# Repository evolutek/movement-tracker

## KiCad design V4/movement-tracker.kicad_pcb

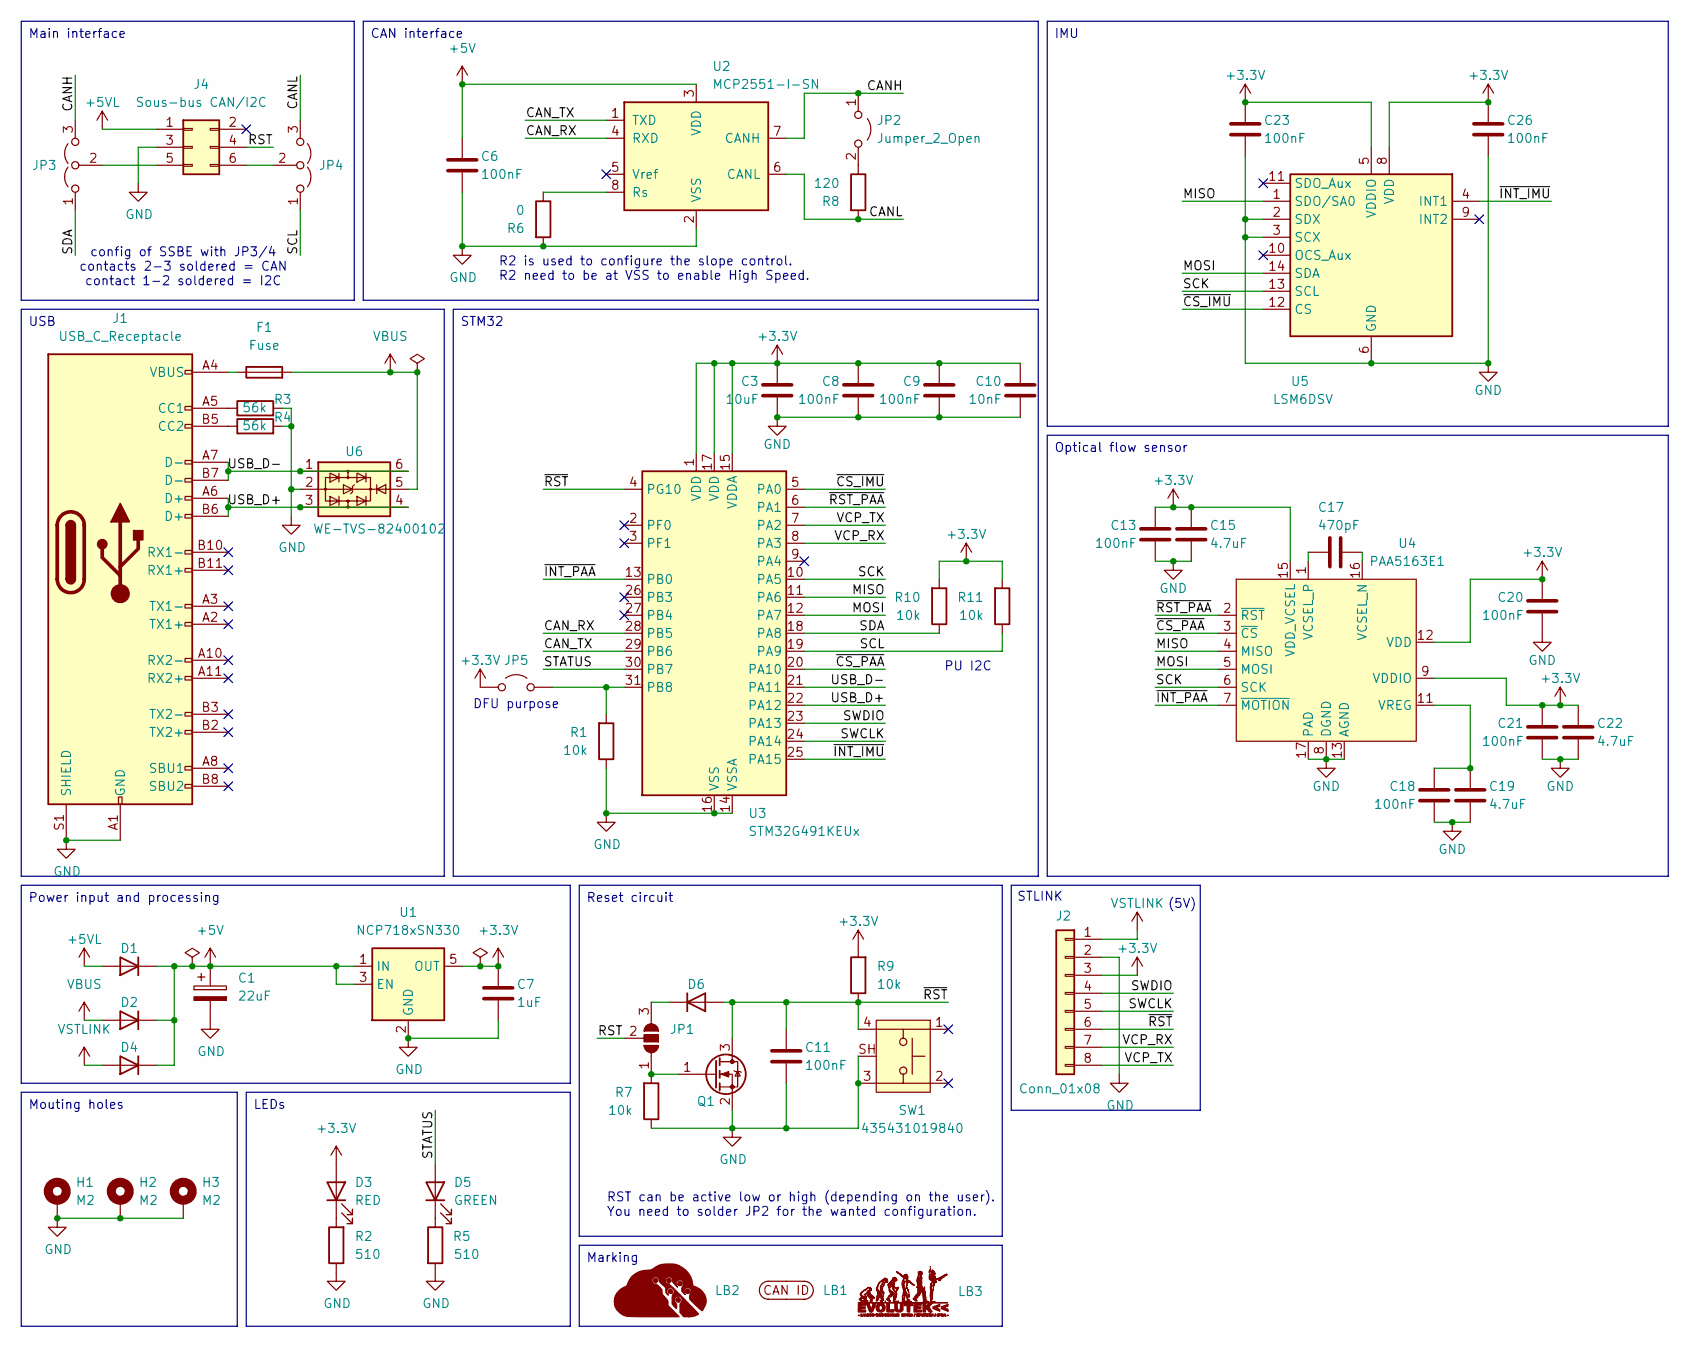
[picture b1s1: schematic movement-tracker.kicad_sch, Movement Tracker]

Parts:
C1: 22uF; CP_Elec_3x5.4
C3: 10uF; C_0603_1608Metric
C6, C8, C9, C11, C13, C18, C20, C21, C23, C26: 100nF; C_0603_1608Metric
C7: 1uF; C_0603_1608Metric
C10: 10nF; C_0603_1608Metric
C15, C19, C22: 4.7uF; C_0603_1608Metric
C17: 470pF; C_0603_1608Metric
D1, D2, D4, D6: D; D_SOD-523
D3: RED; LED_0805_2012Metric
D5: GREEN; LED_0805_2012Metric
F1: Fuse; Fuse_0805_2012Metric
H1, H2, H3: M2; MountingHole_2.2mm_M2_Pad_Via
J1: USB_C_Receptacle; 632722110112
J2: Conn_01x08; 686108188822
J4: Sous-bus CAN/I2C; 690367280676
JP1: SolderJumper_3_Bridged12; SolderJumper-3_P1.3mm_Open_RoundedPad1.0x1.5mm_NumberLabels
JP2, JP5: Jumper_2_Open; SolderJumper-2_P1.3mm_Open_RoundedPad1.0x1.5mm
JP3, JP4: Jumper_3_Open; SolderJumper-3_P1.3mm_Open_RoundedPad1.0x1.5mm_NumberLabels
LB1: CAN ID Label
LB2: LOGO; Logo Aisler Min
LB3: LOGO; logo-evo-min
Q1: Q_NMOS_GSD; SOT-23
R1, R7, R9, R10, R11: 10k; R_0603_1608Metric
R2, R5: 510; R_0603_1608Metric
R3, R4: 56k; R_0603_1608Metric
R6: 0; R_0603_1608Metric
R8: 120; R_0603_1608Metric
SW1: 435431019840
U1: NCP718xSN330; SOT-23-5
U2: MCP2551-I-SN; SOIC-8_3.9x4.9mm_P1.27mm
U3: STM32G491KEUx; QFN-32-1EP_5x5mm_P0.5mm_EP3.45x3.45mm-Without thermal pad
U4: PAA5163E1
U5: LSM6DSV; LGA-14_3x2.5mm_P0.5mm_LayoutBorder3x4y
U6: WE-TVS-82400102; SOT-23-6

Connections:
+3.3V: C3.1, C7.1, C8.1, C9.1, C10.1, C13.2, C15.2, C20.2, C21.2, C22.2, C23.1, C26.1, D3.2 (A), J2.3, JP5.1 (A), R9.2, R10.2, R11.2, U1.5 (OUT), U3.1 (VDD), U3.15 (VDDA), U3.17 (VDD), U4.9 (VDDIO), U4.12 (VDD), U4.15 (VDD_VCSEL), U5.5 (VDDIO), U5.8 (VDD)
+5V: C1.1, C6.1, D1.1 (K), D2.1 (K), D4.1 (K), U1.1 (IN), U1.3 (EN), U2.3 (VDD)
+5VL: D1.2 (A), J4.1
/CANH: JP2.1 (A), JP3.3 (B), U2.7 (CANH)
/CANL: JP4.3 (B), R8.2, U2.6 (CANL)
/CAN_RX: U2.4 (RXD), U3.28 (PB5)
/CAN_TX: U2.1 (TXD), U3.29 (PB6)
/MISO: U3.11 (PA6), U4.4 (MISO), U5.1 (SDO/SA0)
/MOSI: U3.12 (PA7), U4.5 (MOSI), U5.14 (SDA)
/RST: J4.4, JP1.2 (C)
/SCK: U3.10 (PA5), U4.6 (SCK), U5.13 (SCL)
/SCL: JP4.1 (A), R11.1, U3.19 (PA9)
/SDA: JP3.1 (A), R10.1, U3.18 (PA8)
/STATUS: D5.2 (A), U3.30 (PB7)
/SWCLK: J2.5, U3.24 (PA14)
/SWDIO: J2.4, U3.23 (PA13)
/USB_D+: J1.A6 (D+), J1.B6 (D+), U3.22 (PA12), U6.3, U6.4
/USB_D-: J1.A7 (D-), J1.B7 (D-), U3.21 (PA11), U6.1, U6.6
/VCP_RX: J2.7, U3.8 (PA3)
/VCP_TX: J2.8, U3.7 (PA2)
/~CS_IMU: U3.5 (PA0), U5.12 (CS)
/~CS_PAA: U3.20 (PA10), U4.3 (~CS)
/~INT_IMU: U3.25 (PA15), U5.4 (INT1)
/~INT_PAA: U3.13 (PB0), U4.7 (~MOTION)
/~RST_PAA: U3.6 (PA1), U4.2 (~RST)
/~RST: C11.1, D6.2 (A), J2.6, Q1.3 (D), R9.1, SW1.4, U3.4 (PG10)
GND: C1.2, C3.2, C6.2, C7.2, C8.2, C9.2, C10.2, C11.2, C13.1, C15.1, C18.1, C19.1, C20.1, C21.1, C22.1, C23.2, C26.2, H1.1, H2.1, H3.1, J1.A1 (GND), J1.A12 (GND), J1.B1 (GND), J1.B12 (GND), J1.S1 (SHIELD), J2.2, J4.3, Q1.2 (S), R1.1, R2.1, R3.2, R4.2, R5.2, R6.2, R7.1, SW1.3, SW1.SH, U1.2 (GND), U2.2 (VSS), U3.14 (VSSA), U3.16 (VSS), U3.32 (VSS), U4.8 (DGND), U4.13 (AGND), U4.17 (PAD), U5.2 (SDX), U5.3 (SCX), U5.6 (GND), U5.7 (GND), U6.2
unnamed: D3.1 (K), R2.2
unnamed: D5.1 (K), R5.1
unnamed: D6.1 (K), JP1.3 (B)
unnamed: F1.1, J1.A4 (VBUS), J1.A9 (VBUS), J1.B4 (VBUS), J1.B9 (VBUS)
unnamed: J1.A5 (CC1), R3.1
unnamed: J1.B5 (CC2), R4.1
unnamed: J4.5, JP3.2 (C)
unnamed: J4.6, JP4.2 (C)
unnamed: JP1.1 (A), Q1.1 (G), R7.2
unnamed: JP2.2 (B), R8.1
unnamed: JP5.2 (B), R1.2, U3.31 (PB8)
unnamed: R6.1, U2.8 (Rs)
unnamed: C17.1, U4.16 (VCSEL_N)
unnamed: C17.2, U4.1 (VCSEL_P)
unnamed: C18.2, C19.2, U4.11 (VREG)
VBUS: D2.2 (A), F1.2, U6.5
VSTLINK: D4.2 (A), J2.1

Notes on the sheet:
(5V)
PU I2C
DFU purpose
config of SSBE with JP3/4 contacts 2-3 soldered = CAN contact 1-2 soldered = I2C
STLINK
RST can be active low or high (depending on the user). You need to solder JP2 for the wanted configuration.
R2 is used to configure the slope control. R2 need to be at VSS to enable High Speed.
Optical flow sensor
Power input and processing
Reset circuit
IMU
CAN interface
Mouting holes
USB
Marking
STM32
LEDs
Main interface

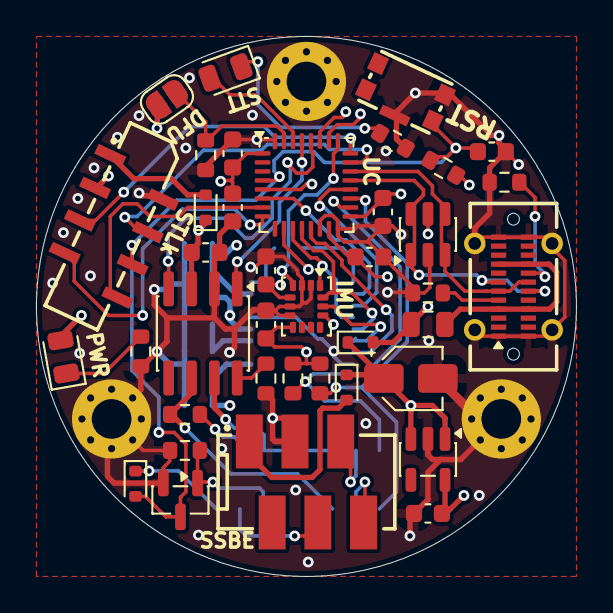
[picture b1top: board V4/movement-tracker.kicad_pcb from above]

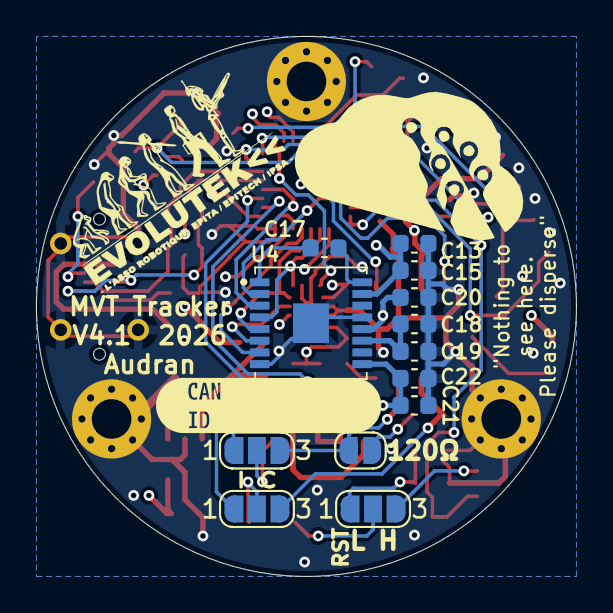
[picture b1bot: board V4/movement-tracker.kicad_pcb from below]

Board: 4 copper layers, 30.0 x 30.0 mm, 58 parts (16 on the bottom side), 44 nets.

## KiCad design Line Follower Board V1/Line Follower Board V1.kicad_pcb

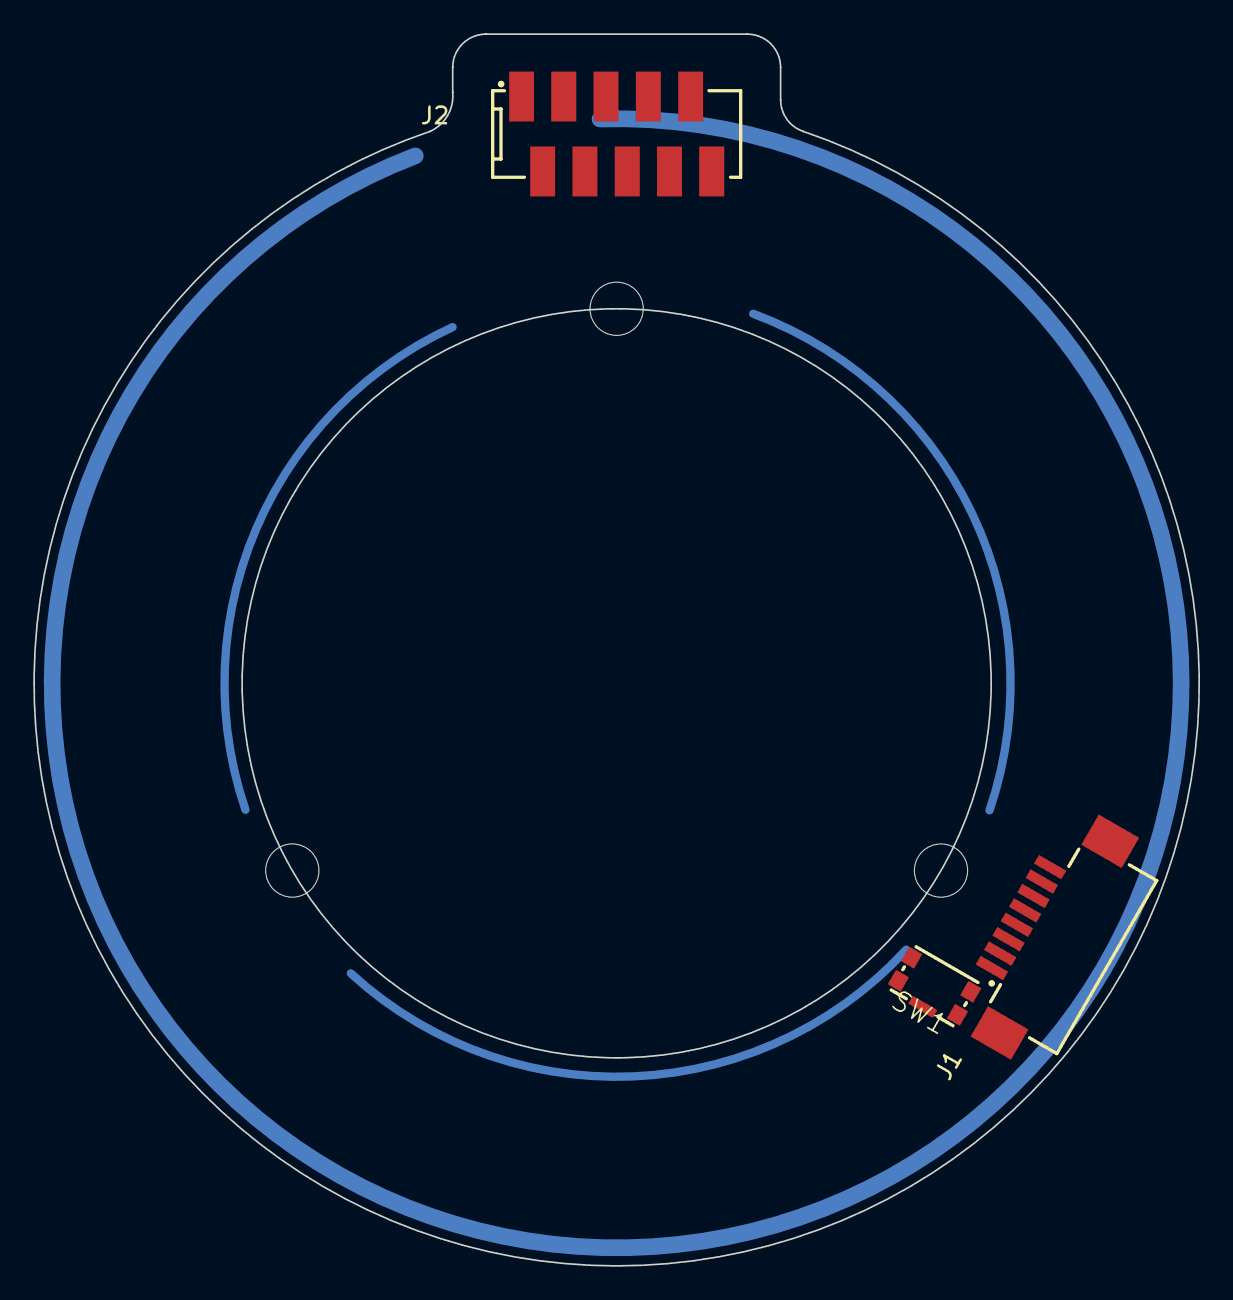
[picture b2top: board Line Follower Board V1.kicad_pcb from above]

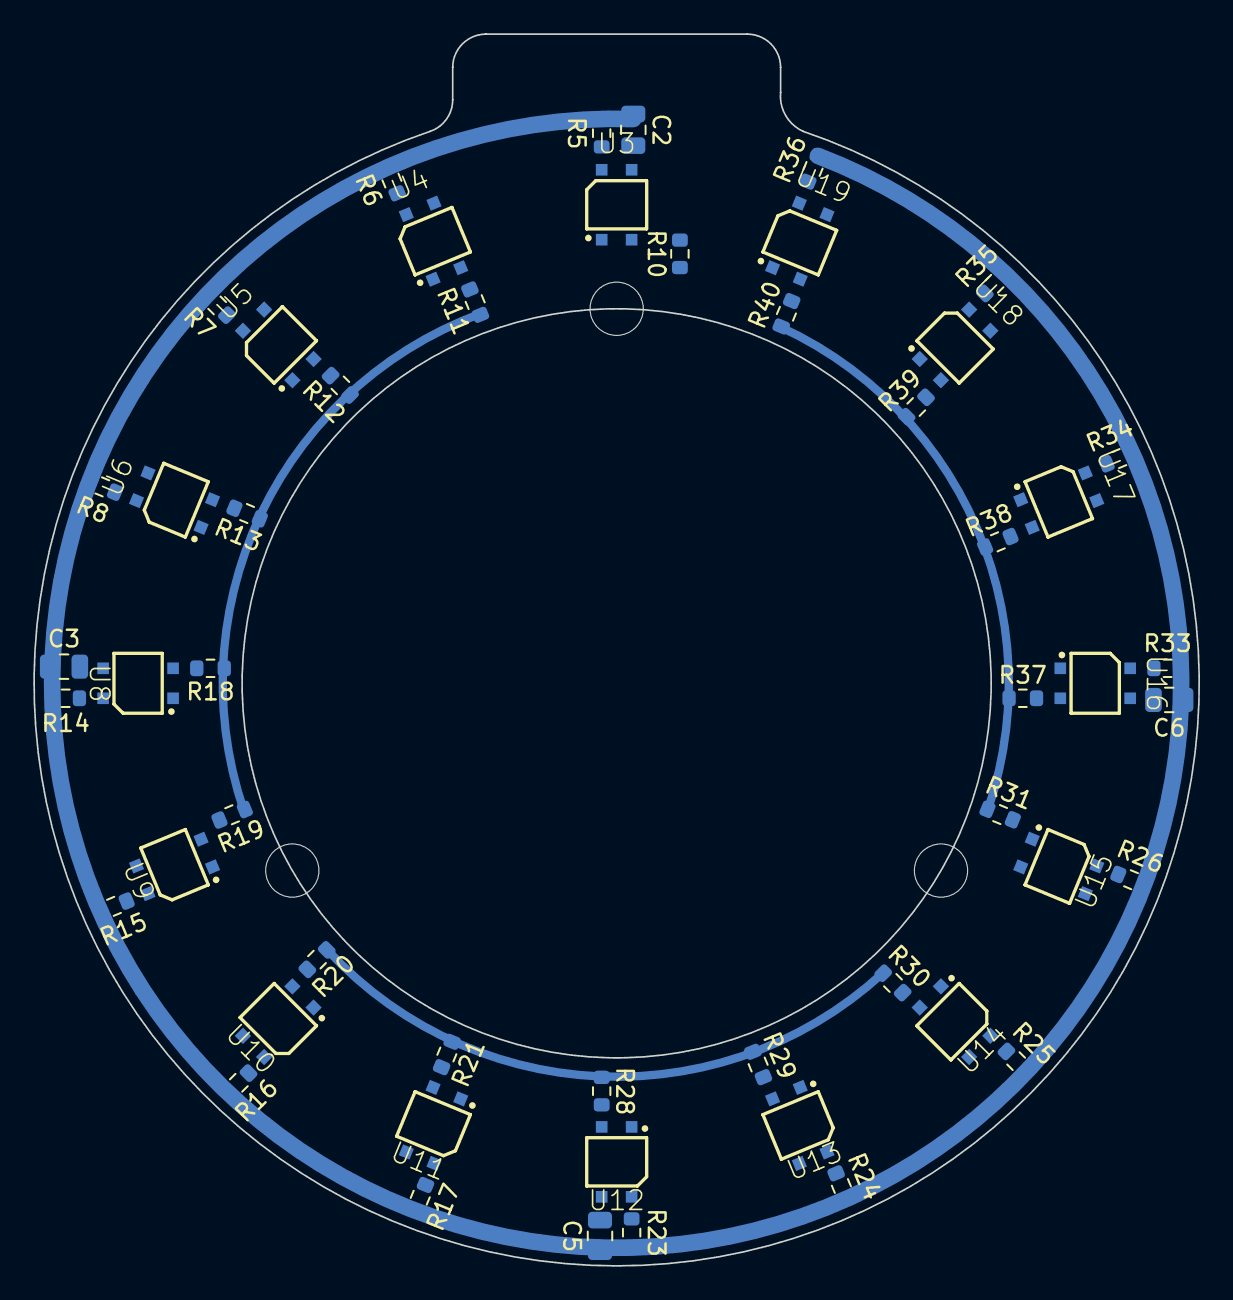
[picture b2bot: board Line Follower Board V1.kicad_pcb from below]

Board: 2 copper layers, 70.0 x 74.0 mm, 58 parts (52 on the bottom side), 36 nets, no tracks yet.

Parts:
C2, C3, C5, C6: 22uF; C_0805_2012Metric
H1, H2, H3: M3; MountingHole_3.2mm_M3
J1: STLINK-EVO; 686108188622
J2: Bus Actuators; 690367281076
R5, R6, R7, R8, R14, R15, R16, R17, R23, R24, R25, R26, R33, R34, R35, R36: 100; R_0603_1608Metric
R10, R11, R12, R13, R18, R19, R20, R21, R28, R29, R30, R31, R37, R38, R39, R40: 10k; R_0603_1608Metric
SW1: 435431019840
U3, U4, U5, U6, U8, U9, U10, U11, U12, U13, U14, U15, U16, U17, U18, U19: 1642730961200; WL-OSEN_2734_1642730961200

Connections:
+3.3V: J1.1, R10.1, R11.1, R12.1, R13.1, R18.1, R19.1, R20.1, R21.1, R28.1, R29.1, R30.1, R31.1, R37.1, R38.1, R39.1, R40.1
+5V: C2.1, C3.1, C5.1, C6.1, J2.1, R5.1, R6.1, R7.1, R8.1, R14.1, R15.1, R16.1, R17.1, R23.1, R24.1, R25.1, R26.1, R33.1, R34.1, R35.1, R36.1
/SENSOR1: R10.2, U3.4
/SENSOR2: R11.2, U4.4
/SENSOR3: R12.2, U5.4
/SENSOR4: R13.2, R18.2, U6.4, U8.4
/SENSOR5: R19.2, U9.4
/SENSOR6: R20.2, U10.4
/SENSOR7: R21.2, U11.4
/SENSOR8: R28.2, U12.4
/SENSOR10: R29.2, U13.4
/SENSOR11: R30.2, U14.4
/SENSOR12: R31.2, U15.4
/SENSOR13: R37.2, U16.4
/SENSOR14: R38.2, U17.4
/SENSOR15: R39.2, U18.4
/SENSOR16: R40.2, U19.4
/~RST: J1.5, SW1.4
GND: J1.4, J1.8, J1.MP (MountPin), J2.3, J2.4, SW1.3, SW1.SH, U3.3, U4.3, U5.3, U6.3, U8.3, U9.3, U10.3, U11.3, U12.3, U13.3, U14.3, U15.3, U16.3, U17.3, U18.3, U19.3
GNDS: C2.2, C3.2, C5.2, C6.2, U3.1 (K), U4.1 (K), U5.1 (K), U6.1 (K), U8.1 (K), U9.1 (K), U10.1 (K), U11.1 (K), U12.1 (K), U13.1 (K), U14.1 (K), U15.1 (K), U16.1 (K), U17.1 (K), U18.1 (K), U19.1 (K)
unnamed: R5.2, U3.2 (A)
unnamed: R6.2, U4.2 (A)
unnamed: R7.2, U5.2 (A)
unnamed: R8.2, U6.2 (A)
unnamed: R14.2, U8.2 (A)
unnamed: R15.2, U9.2 (A)
unnamed: R16.2, U10.2 (A)
unnamed: R17.2, U11.2 (A)
unnamed: R23.2, U12.2 (A)
unnamed: R24.2, U13.2 (A)
unnamed: R25.2, U14.2 (A)
unnamed: R26.2, U15.2 (A)
unnamed: R33.2, U16.2 (A)
unnamed: R34.2, U17.2 (A)
unnamed: R35.2, U18.2 (A)
unnamed: R36.2, U19.2 (A)

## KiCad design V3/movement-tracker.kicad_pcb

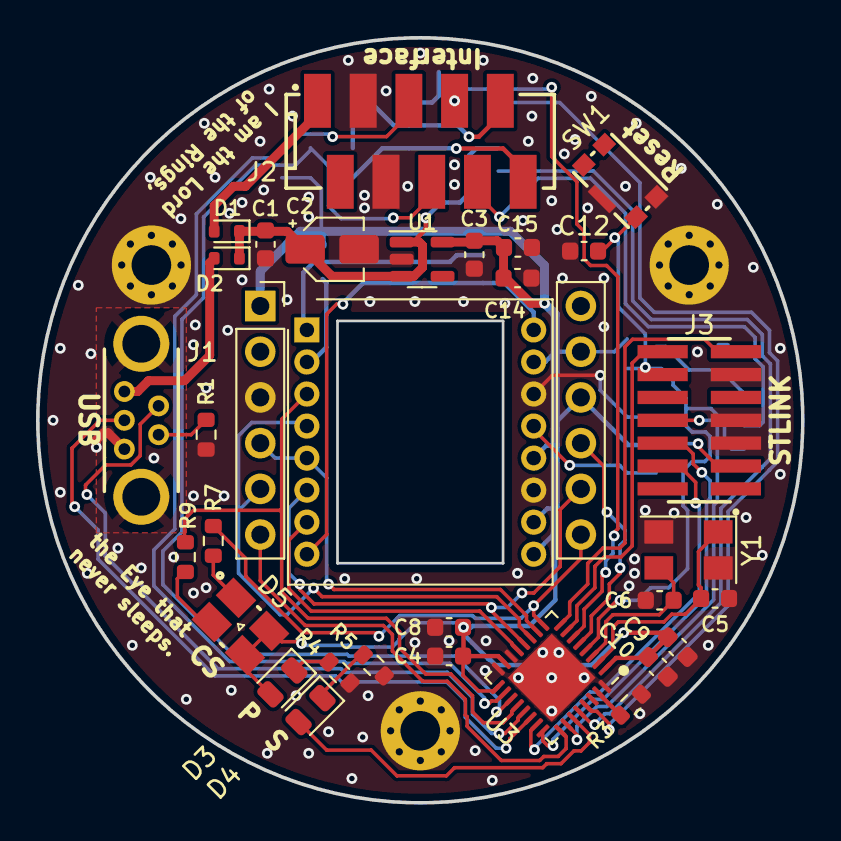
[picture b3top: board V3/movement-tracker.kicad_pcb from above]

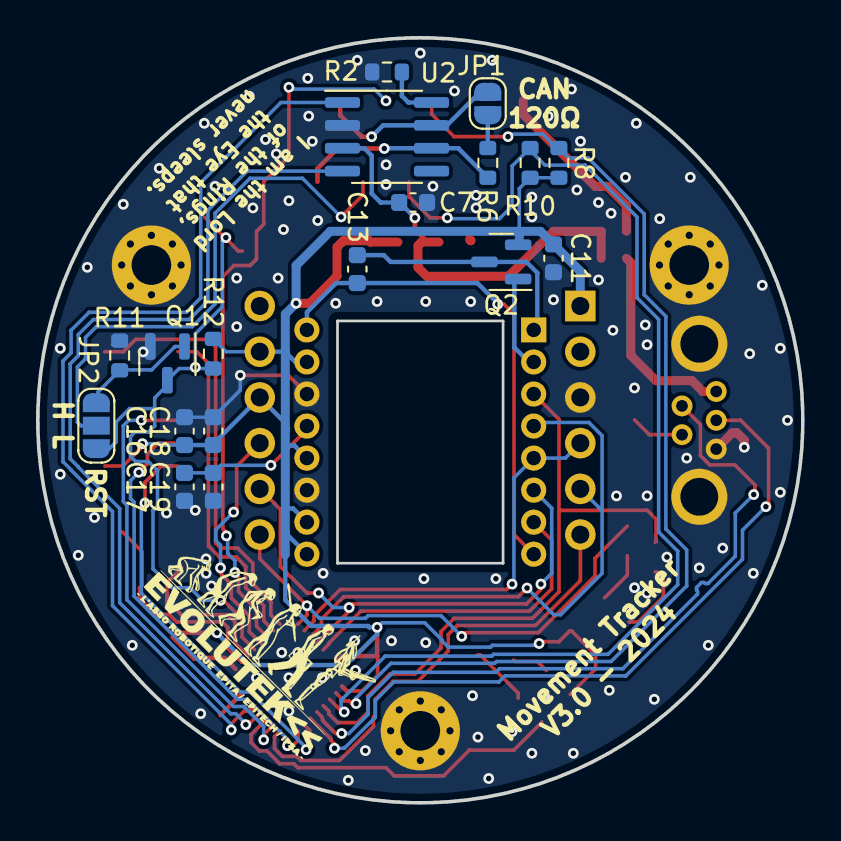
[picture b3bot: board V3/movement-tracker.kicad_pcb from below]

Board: 2 copper layers, 42.5 x 42.5 mm, 53 parts (18 on the bottom side), 45 nets.

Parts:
C1, C3, C15: 1uF; C_0603_1608Metric
C2: 100uF; CP_Elec_3x5.4
C4, C19: 10uF; C_0603_1608Metric
C5, C6: 18pF; C_0603_1608Metric
C7, C8, C9, C11, C12, C14, C16, C17: 100nF; C_0603_1608Metric
C10: 10nF; C_0603_1608Metric
C13: 470p; C_0603_1608Metric
C18: 3.3uF; C_0603_1608Metric
D1, D2: D; D_SOD-523
D3: RED; LED_0805_2012Metric
D4: GREEN; LED_0805_2012Metric
D5: 150121YV74000; WL-SBCW_1210
H1, H2, H3: M2; MountingHole_2.2mm_M2_Pad_Via
J1: USB_B_Mini; 651005136421
J2: Bus Actuators; 690367281076
J3: STLINK; SAMTEC_FTSH-107-01-L-DV-K
JP1: Jumper_2_Open; SolderJumper-2_P1.3mm_Open_RoundedPad1.0x1.5mm
JP2: SolderJumper_3_Bridged12; SolderJumper-3_P1.3mm_Open_RoundedPad1.0x1.5mm_NumberLabels
Q1: Q_NMOS_GSD; SOT-23
Q2: Q_PMOS_GSD; SOT-23
R1: 100k; R_0603_1608Metric
R2: 0; R_0603_1608Metric
R3, R11, R12: 10k; R_0603_1608Metric
R4, R5, R7, R9: 510; R_0603_1608Metric
R6: 120; R_0603_1608Metric
R8, R10: 4.7k; R_0603_1608Metric
SW1: 435431019840
U1: NCP718xSN330; SOT-23-5
U2: MCP2551-I-SN; SOIC-8_3.9x4.9mm_P1.27mm
U3: STM32G491KEUx; QFN-32-1EP_5x5mm_P0.5mm_EP3.45x3.45mm
U4: BNO085; Adafruit BNO085
U5: ADNS 9800
Y1: 16 MHz; Crystal_SMD_5032-4Pin_5.0x3.2mm

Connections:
+3.3V: C3.1, C4.1, C8.1, C9.1, C10.1, C11.1, C14.1, C15.1, C16.1, C18.1, D3.2 (A), D5.3 (AG), D5.4 (AY), J3.3, Q2.2 (S), R8.1, R10.1, R12.2, U1.5 (OUT), U3.1 (VDD), U3.15 (VDDA), U3.17 (VDD), U4.1 (VIN), U4.8 (P0), U4.9 (P1), U5.9 (VDD), U5.10 (PWR_OPT), U5.12 (VDD3), U5.15 (VDDIO)
+5V: C1.1, C2.1, C7.1, D1.1 (K), D2.1 (K), U1.1 (IN), U1.3 (EN), U2.3 (VDD)
+5VA: D1.2 (A), J2.1
/AU/~INT: J2.7, U3.6 (PA1)
/CANH: J2.9, JP1.1 (A), U2.7 (CANH)
/CANL: J2.10, R6.2, U2.6 (CANL)
/CAN_RX: U2.4 (RXD), U3.28 (PB5)
/CAN_TX: U2.1 (TXD), U3.29 (PB6)
/MISO: U3.11 (PA6), U4.5 (SDA/MISO/RX), U5.4 (MISO)
/MOSI: U3.12 (PA7), U4.11 (A0/MOSI), U5.6 (MOSI)
/RST: J2.8, JP2.2 (C)
/SCK: U3.10 (PA5), U4.4 (SCL/CLK/TX), U5.5 (CLK)
/SCL: J2.6, R10.2, U3.19 (PA9)
/SDA: J2.5, R8.2, U3.18 (PA8)
/STATUS: D4.2 (A), U3.27 (PB4)
/SWCLK: J3.6, U3.24 (PA14)
/SWDIO: J3.4, U3.23 (PA13)
/SWO: J3.8, U3.26 (PB3)
/USB_D+: J1.3 (D+), U3.22 (PA12)
/USB_D-: J1.2 (D-), U3.21 (PA11)
/VCP_RX: J3.13, U3.8 (PA3)
/VCP_TX: J3.14, U3.7 (PA2)
/~CS_ADNS: R9.1, U3.20 (PA10), U5.3 (~CS)
/~CS_IMU: R7.1, U3.9 (PA4), U4.12 (~CS)
/~INT_ADNS: U3.13 (PB0), U5.7 (~MOTION)
/~INT_IMU: U3.25 (PA15), U4.6 (~INT)
/~RST_IMU: U3.5 (PA0), U4.10 (~RST)
/~RST: C12.1, J3.12, JP2.3 (B), Q1.3 (D), R12.1, SW1.4, U3.4 (PG10)
GND: C1.2, C2.2, C3.2, C4.2, C5.1, C6.1, C7.2, C8.2, C9.2, C10.2, C11.2, C12.2, C14.2, C15.2, C16.2, C17.2, C18.2, C19.2, H1.1, H2.1, H3.1, J1.5 (GND), J1.6 (Shield), J2.3, J2.4, J3.5, J3.7, J3.11, Q1.2 (S), R1.1, R2.2, R3.2, R4.1, R5.1, R11.1, SW1.3, SW1.SH, U1.2 (GND), U2.2 (VSS), U3.14 (VSSA), U3.16 (VSS), U3.32 (VSS), U3.33 (VSS), U4.3 (GND), U5.11 (GND), U5.14 (D_GND), Y1.2, Y1.4
unnamed: D3.1 (K), R4.2
unnamed: D4.1 (K), R5.2
unnamed: D5.2 (KG), R9.2
unnamed: D5.1 (KY), R7.2
unnamed: J1.4 (ID), R1.2
unnamed: JP1.2 (B), R6.1
unnamed: JP2.1 (A), Q1.1 (G), R11.2
unnamed: C13.1, Q2.3 (D), U5.1 (+VCSEL)
unnamed: Q2.1 (G), U5.2 (LASER_NEN)
unnamed: R2.1, U2.8 (Rs)
unnamed: R3.1, U3.31 (PB8)
unnamed: C5.2, U3.2 (PF0), Y1.1
unnamed: C6.2, U3.3 (PF1), Y1.3
unnamed: C13.2, U5.8 (XYLASER), U5.16 (-VCSEL)
unnamed: C17.1, C19.1, U5.13 (REFA)
VBUS: D2.2 (A), J1.1 (VBUS)

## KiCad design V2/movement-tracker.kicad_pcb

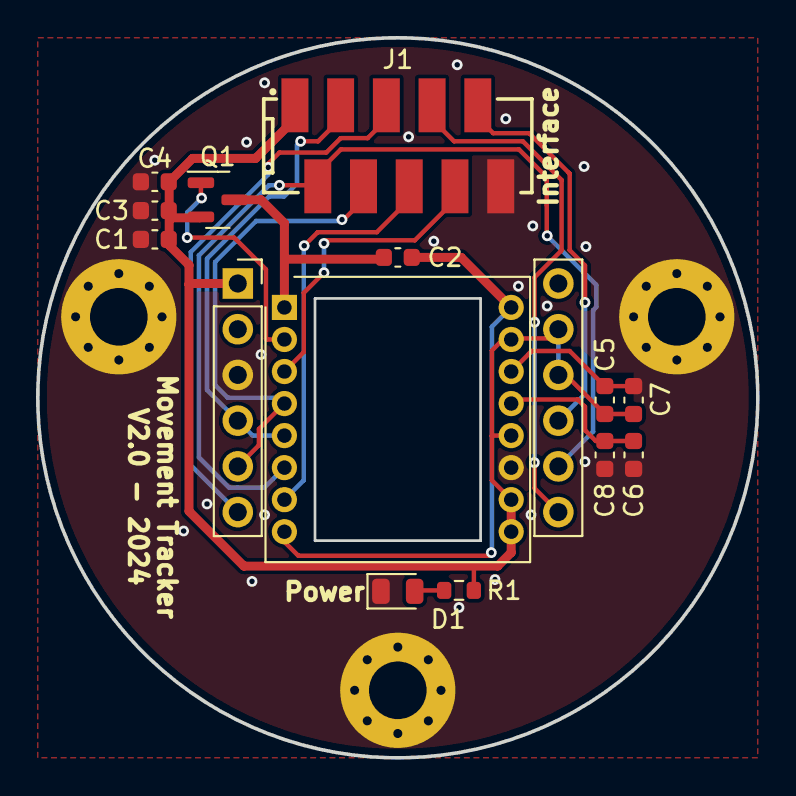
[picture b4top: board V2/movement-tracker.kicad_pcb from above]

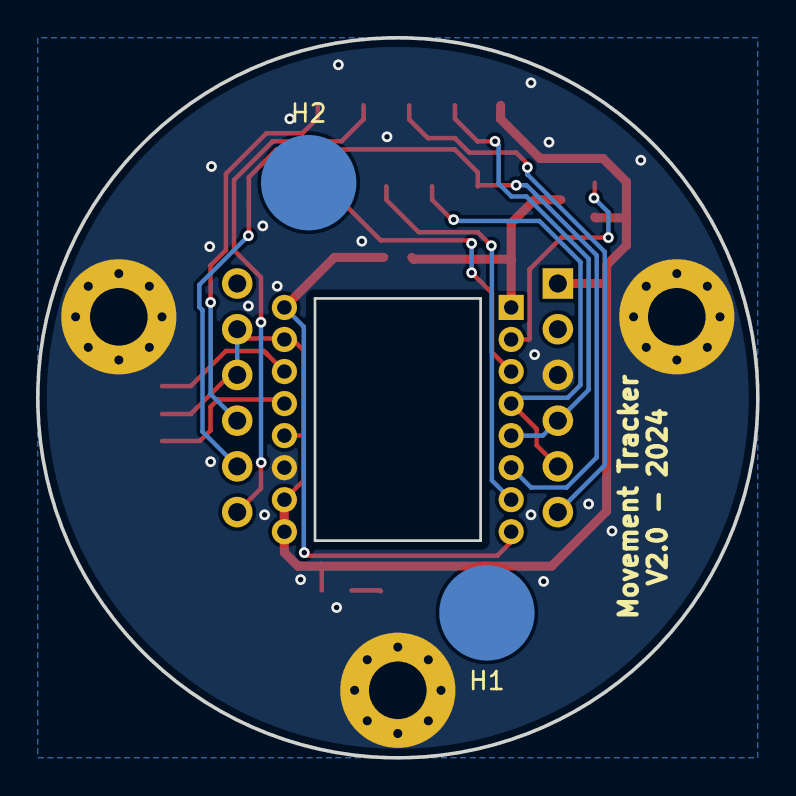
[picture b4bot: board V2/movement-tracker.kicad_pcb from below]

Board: 2 copper layers, 40.0 x 40.0 mm, 19 parts (2 on the bottom side), 15 nets.

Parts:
C1, C3, C5, C6: 100n; C_0603_1608Metric
C2: 470p; C_0603_1608Metric
C4: 1u; C_0603_1608Metric
C7: 3.3u; C_0603_1608Metric
C8: 10u; C_0603_1608Metric
D1: RED; LED_0805_2012Metric
H1, H2: M2; WA-SMSI_9774015243_Reversed
H3, H4, H5: M3; MountingHole_3.2mm_M3_Pad_Via
J1: Conn_02x05_Odd_Even; 690367281076
Q1: Q_PMOS_GSD; SOT-23
R1: 510; R_0603_1608Metric
U1: Adafruit BNO085
U2: ADNS 9800

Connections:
+3V3: C1.1, C3.1, C4.1, C5.1, C7.1, J1.1, Q1.2 (S), R1.2, U1.1 (VIN), U1.8 (P0), U1.9 (P1), U2.9 (VDD), U2.10 (PWR_OPT), U2.12 (VDD3), U2.15 (VDDIO)
/MISO: J1.4, U1.5 (SDA/MISO/RX), U2.4 (MISO)
/MOSI: J1.2, U1.11 (A0/MOSI), U2.6 (MOSI)
/SCK: J1.3, U1.4 (SCL/CLK/TX), U2.5 (CLK)
/~CS_ADNS: J1.8, U2.3 (~CS)
/~CS_IMU: J1.7, U1.12 (~CS)
/~INT_ADNS: J1.6, U2.7 (~MOTION)
/~INT_IMU: J1.5, U1.6 (~INT)
/~RST_IMU: J1.9, U1.10 (~RST)
GND: C1.2, C3.2, C4.2, C5.2, C6.2, C7.2, C8.2, D1.1 (K), H3.1, H4.1, H5.1, J1.10, U1.3 (GND), U2.11 (GND), U2.14 (D_GND)
unnamed: D1.2 (A), R1.1
unnamed: C2.1, Q1.3 (D), U2.1 (+VCSEL)
unnamed: Q1.1 (G), U2.2 (LASER_NEN)
unnamed: C2.2, U2.8 (XYLASER), U2.16 (-VCSEL)
unnamed: C6.1, C8.1, U2.13 (REFA)

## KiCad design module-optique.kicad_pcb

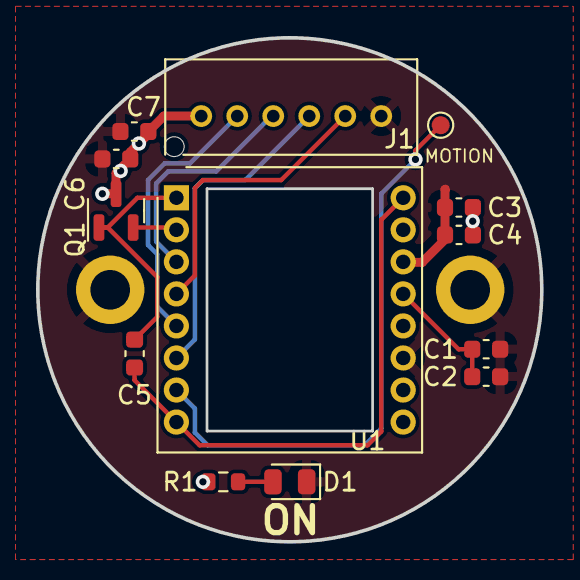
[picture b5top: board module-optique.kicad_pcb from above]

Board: 2 copper layers, 28.0 x 28.0 mm, 16 parts (1 on the bottom side), 12 nets.

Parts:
C1, C3, C6: 100n; C_0603_1608Metric
C2: 10u; C_0603_1608Metric
C4: 3.3u; C_0603_1608Metric
C5: 470p; C_0603_1608Metric
C7: 1u; C_0603_1608Metric
D1: LED; LED_0805_2012Metric
H1, H2: M2; MountingHole_2.2mm_M2_DIN965_Pad
J1: Conn_01x06; B06B-PASK
LOGO1: TestPoint_Small; logo-evo-micro
Q1: PMOS; SOT-23
R1: 510; R_0603_1608Metric
TP1: TestPoint; TestPoint_Pad_D1.0mm
U1: ADNS 9800; ADNS-9800

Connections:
+3V3: C3.1, C4.1, C6.1, C7.1, J1.1, Q1.3 (S), R1.1, U1.9 (VDD), U1.10 (PWR_OPT), U1.12 (VDD3), U1.15 (VDDIO)
/CS: J1.3, U1.3 (~CS)
/MISO: J1.5, U1.4 (MISO)
/MOSI: J1.4, U1.6 (MOSI)
/SCK: J1.2, U1.5 (CLK)
GND: C1.2, C2.2, C3.2, C4.2, C6.2, C7.2, D1.1 (K), H1.1, H2.1, J1.6, U1.11 (GND), U1.14 (D_GND)
unnamed: D1.2 (A), R1.2
unnamed: C5.1, Q1.1 (D), U1.1 (+VCSEL)
unnamed: Q1.2 (G), U1.2 (LASER_NEN)
unnamed: C5.2, U1.8 (XYLASER), U1.16 (-VCSEL)
unnamed: C1.1, C2.1, U1.13 (REFA)
unnamed: TP1.1, U1.7 (~MOTION)

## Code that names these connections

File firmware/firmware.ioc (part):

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Mcu.Name=STM32G491K(C-E)Ux
Mcu.Package=UFQFPN32
Mcu.UserName=STM32G491KEUx
PA0.GPIOParameters=PinState,GPIO_PuPd,GPIO_Label
PA0.GPIO_Label=RST_IMU
PA0.GPIO_PuPd=GPIO_NOPULL
PA0.PinState=GPIO_PIN_SET
PA0.Signal=GPIO_Output
PA1.GPIOParameters=GPIO_PuPd,GPIO_Label
PA1.GPIO_Label=AU/INT
PA1.GPIO_PuPd=GPIO_PULLDOWN
PA1.Signal=SharedStack_PA1
PA1.Stacked=true
PA10.GPIOParameters=GPIO_Speed,PinState,GPIO_Label
PA10.GPIO_Label=CS_ADNS
PA10.GPIO_Speed=GPIO_SPEED_FREQ_VERY_HIGH
PA10.PinState=GPIO_PIN_SET
PA10.Signal=GPIO_Output
PA11.Mode=Device
PA11.Signal=USB_DM
PA12.Mode=Device
PA12.Signal=USB_DP
PA13.GPIOParameters=GPIO_Label
PA13.GPIO_Label=SWDIO
PA13.Mode=Trace_Asynchronous_SW
PA13.Signal=SYS_JTMS-SWDIO
PA14.GPIOParameters=GPIO_Label
PA14.GPIO_Label=SWCLK
PA14.Mode=Trace_Asynchronous_SW
PA14.Signal=SYS_JTCK-SWCLK
PA15.GPIOParameters=GPIO_PuPd,GPIO_Label,GPIO_ModeDefaultEXTI
PA15.GPIO_Label=INT_IMU
PA15.GPIO_ModeDefaultEXTI=GPIO_MODE_IT_FALLING
PA15.GPIO_PuPd=GPIO_PULLUP
PA15.Signal=GPXTI15
PA2.Mode=Asynchronous
PA2.Signal=USART2_TX
PA3.Mode=Asynchronous
PA3.Signal=USART2_RX
PA4.GPIOParameters=GPIO_Speed,PinState,GPIO_Label
PA4.GPIO_Label=CS_IMU
PA4.GPIO_Speed=GPIO_SPEED_FREQ_VERY_HIGH
PA4.PinState=GPIO_PIN_SET
PA4.Signal=GPIO_Output
PA5.Mode=Full_Duplex_Master
PA5.Signal=SPI1_SCK
PA6.Mode=Full_Duplex_Master
PA6.Signal=SPI1_MISO
PA7.Mode=Full_Duplex_Master
PA7.Signal=SPI1_MOSI
PA8.Mode=I2C
PA8.Signal=I2C2_SDA
PA9.Mode=I2C
PA9.Signal=I2C2_SCL
PB0.GPIOParameters=GPIO_PuPd,GPIO_Label
PB0.GPIO_Label=INT_ANDS
PB0.GPIO_PuPd=GPIO_PULLUP
PB0.Signal=GPXTI0
PB3.GPIOParameters=GPIO_Label
PB3.GPIO_Label=SWO
PB3.Mode=Trace_Asynchronous_SW
PB3.Signal=SYS_JTDO-SWO
PB4.GPIOParameters=GPIO_Label
PB4.GPIO_Label=STATUS
PB4.Signal=GPIO_Output
PB5.GPIOParameters=GPIO_Label
PB5.GPIO_Label=CAN_RX
PB5.Mode=FDCAN_Activate
PB5.Signal=FDCAN2_RX
PB6.GPIOParameters=GPIO_Label
PB6.GPIO_Label=CAN_TX
PB6.Mode=FDCAN_Activate
PB6.Signal=FDCAN2_TX
RCC.HSE_VALUE=8000000
RCC.SYSCLKFreq_VALUE=48000000
RCC.SYSCLKSource=RCC_SYSCLKSOURCE_PLLCLK
board=custom

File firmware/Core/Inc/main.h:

/* USER CODE BEGIN Header */
/**
  ******************************************************************************
  * @file           : main.h
  * @brief          : Header for main.c file.
  *                   This file contains the common defines of the application.
  ******************************************************************************
  * @attention
  *
  * Copyright (c) 2023 STMicroelectronics.
  * All rights reserved.
  *
  * This software is licensed under terms that can be found in the LICENSE file
  * in the root directory of this software component.
  * If no LICENSE file comes with this software, it is provided AS-IS.
  *
  ******************************************************************************
  */
/* USER CODE END Header */

/* Define to prevent recursive inclusion -------------------------------------*/
#ifndef __MAIN_H
#define __MAIN_H

#ifdef __cplusplus
extern "C" {
#endif

/* Includes ------------------------------------------------------------------*/
#include "stm32g4xx_hal.h"

/* Private includes ----------------------------------------------------------*/
/* USER CODE BEGIN Includes */

/* USER CODE END Includes */

/* Exported types ------------------------------------------------------------*/
/* USER CODE BEGIN ET */

/* USER CODE END ET */

/* Exported constants --------------------------------------------------------*/
/* USER CODE BEGIN EC */
extern SPI_HandleTypeDef hspi1;
extern I2C_HandleTypeDef hi2c2;
/* USER CODE END EC */

/* Exported macro ------------------------------------------------------------*/
/* USER CODE BEGIN EM */

/* USER CODE END EM */

/* Exported functions prototypes ---------------------------------------------*/
void Error_Handler(void);

/* USER CODE BEGIN EFP */

/* USER CODE END EFP */

/* Private defines -----------------------------------------------------------*/
#define RST_IMU_Pin GPIO_PIN_0
#define RST_IMU_GPIO_Port GPIOA
#define RST_PAA_Pin GPIO_PIN_1
#define RST_PAA_GPIO_Port GPIOA
#define VCP_TX_Pin GPIO_PIN_2
#define VCP_TX_GPIO_Port GPIOA
#define VCP_RX_Pin GPIO_PIN_3
#define VCP_RX_GPIO_Port GPIOA
#define CS_IMU_Pin GPIO_PIN_4
#define CS_IMU_GPIO_Port GPIOA
#define SCK_Pin GPIO_PIN_5
#define SCK_GPIO_Port GPIOA
#define MISO_Pin GPIO_PIN_6
#define MISO_GPIO_Port GPIOA
#define MOSI_Pin GPIO_PIN_7
#define MOSI_GPIO_Port GPIOA
#define INT_PAA_Pin GPIO_PIN_0
#define INT_PAA_GPIO_Port GPIOB
#define SDA_Pin GPIO_PIN_8
#define SDA_GPIO_Port GPIOA
#define SCL_Pin GPIO_PIN_9
#define SCL_GPIO_Port GPIOA
#define CS_PAA_Pin GPIO_PIN_10
#define CS_PAA_GPIO_Port GPIOA
#define SWDIO_Pin GPIO_PIN_13
#define SWDIO_GPIO_Port GPIOA
#define SWCLK_Pin GPIO_PIN_14
#define SWCLK_GPIO_Port GPIOA
#define INT_IMU_Pin GPIO_PIN_15
#define INT_IMU_GPIO_Port GPIOA
#define SWO_Pin GPIO_PIN_3
#define SWO_GPIO_Port GPIOB
#define AU_INT_Pin GPIO_PIN_4
#define AU_INT_GPIO_Port GPIOB
#define CAN_RX_Pin GPIO_PIN_5
#define CAN_RX_GPIO_Port GPIOB
#define CAN_TX_Pin GPIO_PIN_6
#define CAN_TX_GPIO_Port GPIOB
#define STATUS_Pin GPIO_PIN_7
#define STATUS_GPIO_Port GPIOB

/* USER CODE BEGIN Private defines */

/* USER CODE END Private defines */

#ifdef __cplusplus
}
#endif

#endif /* __MAIN_H */

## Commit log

2023-09-19 backup
2023-09-20 Silkscreen edit
2023-09-20 minor fix
2023-09-20 Module Optique V1.0
2023-09-21 Added 3D for the ADNS sensor
2023-09-21 Added 3D for the ADNS 9800
2023-09-22 made a bigger version
    to accommodate for lens mounting
2023-09-23 reorganization
2023-09-23 modifications for the bigger version, and 3D
2023-09-24 Generate output files
2023-10-07 Put Module optique boards into V1 folder
2023-10-08 Wip of the movement tracker V2
2023-10-09 Movement Tracker V2
2023-12-28 Movement Tracker V3.0
2023-12-29 Add base firmware
2024-01-06 Add a pulldown resistor on RST
2024-02-23 initial setup of the workspace
2024-02-24 compiles ! but cannot work ...
    need to find an alternative to delayMicroseconds
2024-02-25 got the ADNS9800 to report its position
    need some cleanup and propper formatting, but it's basically done
2024-02-26 minor refacto
2024-02-28 minor rework
2024-03-01 started porting
2024-03-01 able to send and receive packets
2024-03-01 minor cleanup
2024-03-04 ported all the strictly necessary functions
    seem to have ported all the strictly necessary functions for the most basic operation of the sensor to get yaw from the BNO085 - needs testing
2024-03-04 doesn't parse properly
    doesn't want to go into the parse input reports function for some reason
2024-03-04 actually just resets all the time
    resets all the time, which probably causes the reports to roll back to none
2024-03-07 can get a report once
    get one report, then the sensor just resets for no apparent reason
    as such, set_reports appears to be working and isn't the problem
    need more hardware investigation and more checks regarding the behaviour of the bno pins
    so actually, last comits hypothesis were wrong, it seems to parse properly, but i need to further check if the reports are disabled at reset, even tho it's not really a fix and more of a check to bet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
    anyways, need to diagnose this fking repeated reset, which *seems* to happen according to a timestamp, as
2024-03-07 DON'T MERGE THIS ONE !
    bunch of tests, probably broke evertything
    init and ADNS still works tho
2024-03-08 IT WORKS well, almost
    refacto-ed and it works now . . .
    Altho for some bizare reason, the init has to fail in order for the reports to be valid. . .
    and resetting the board breaks it
    still need some investigation
    EDIT : in fact, it works properly only when flashing the firmware, power cycling or resetting breaks it
    EDIT : increaing the delay after reset fixed it, except for the init fail
2024-03-08 init still fails, but it works otherwise
    there's definetly something wrong with the init sequence, but the sensor reports yaw fine
2024-03-08 BNO085 is now operationnal !
    IT FUCKING WORKS NOW !!! WITH NO JENKY BEHAVIOUR !
2024-03-08 report frequency can be increased
    need to check if i'm not attempting to read even tho the int isn't asserted by the chip, as getting rid of the delay in the loop shouldn't break anything
2024-03-08 reading both sensors at once is not a problem
    in great need of some optimisation, but it's working fine
2024-03-09 cleaned up a bit, started working on absolute positionning
2024-03-13 started trying to figure out the I2C comm
2024-03-18 works well, but kinda unreliable atm
2024-03-22 not bad, high speed is an issue tho
2024-04-04 Started trying to work out I2C
2024-04-04 should be able to transmit heading
2024-04-04 spliting the float works
2024-04-05 sending heading works
2024-04-11 rotation control works
2024-04-11 now able to transmit X Y t
2024-04-11 starting to implement commands
2024-04-11 almost there
2024-04-12 now able to receive commands
2024-04-12 can now be set at a specific position
2024-04-12 coordinates are now on the right axies
2024-04-13 relative angle can be set
2024-04-24 way more on yaw axis
2024-05-03 performance improvements
2024-11-16 initial push of V4
2024-11-16 awaiting review
2024-11-16 waiting for review
2025-01-02 added logo and label
2025-01-02 WIP Line follower board
2025-01-02 Release MVT V4.0
2025-02-01 WIP Line Follower Board V1.0
2025-02-20 started BNO firmware
2025-02-21 PAA5163 - polling : done
2025-02-21 both sensors working
    next step is processing of raw bno data and fusion
2025-02-23 trying to interpret bno data
2025-02-23 initial coms with bno working
2025-02-25 started implementing the full SH2 protocol
2025-02-25 sensor resets for unknown reasons
2025-02-25 started implementing adafruit's
2025-02-25 sensor keeps reseting
2025-02-27 goes trough init, but no data
2025-03-02 very weird behaviour
    enabling reports reliably produces a report right after ...
    The sensor just doesn't want to produce reports on its own for some reason
2025-06-24 Clean branch
2026-01-28 init
2026-01-28 Remove trash files
2026-01-28 Schematics for V4.1
2026-02-02 schematic and routing
2026-02-03 reprise du routage complete
    WIP, reste serigraphie, DRC, via stiching
2026-02-05 fin du routage
2026-02-05 fixed via stiching and added ground ring on L3
2026-02-24 Ajout de l'alimentation par le STlink
2026-03-06 V4.1 ready to prod
2026-03-30 Fix output
